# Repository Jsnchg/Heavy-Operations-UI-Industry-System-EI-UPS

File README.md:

# Heavy-Operations-UI-Industry-System-EI-UPS

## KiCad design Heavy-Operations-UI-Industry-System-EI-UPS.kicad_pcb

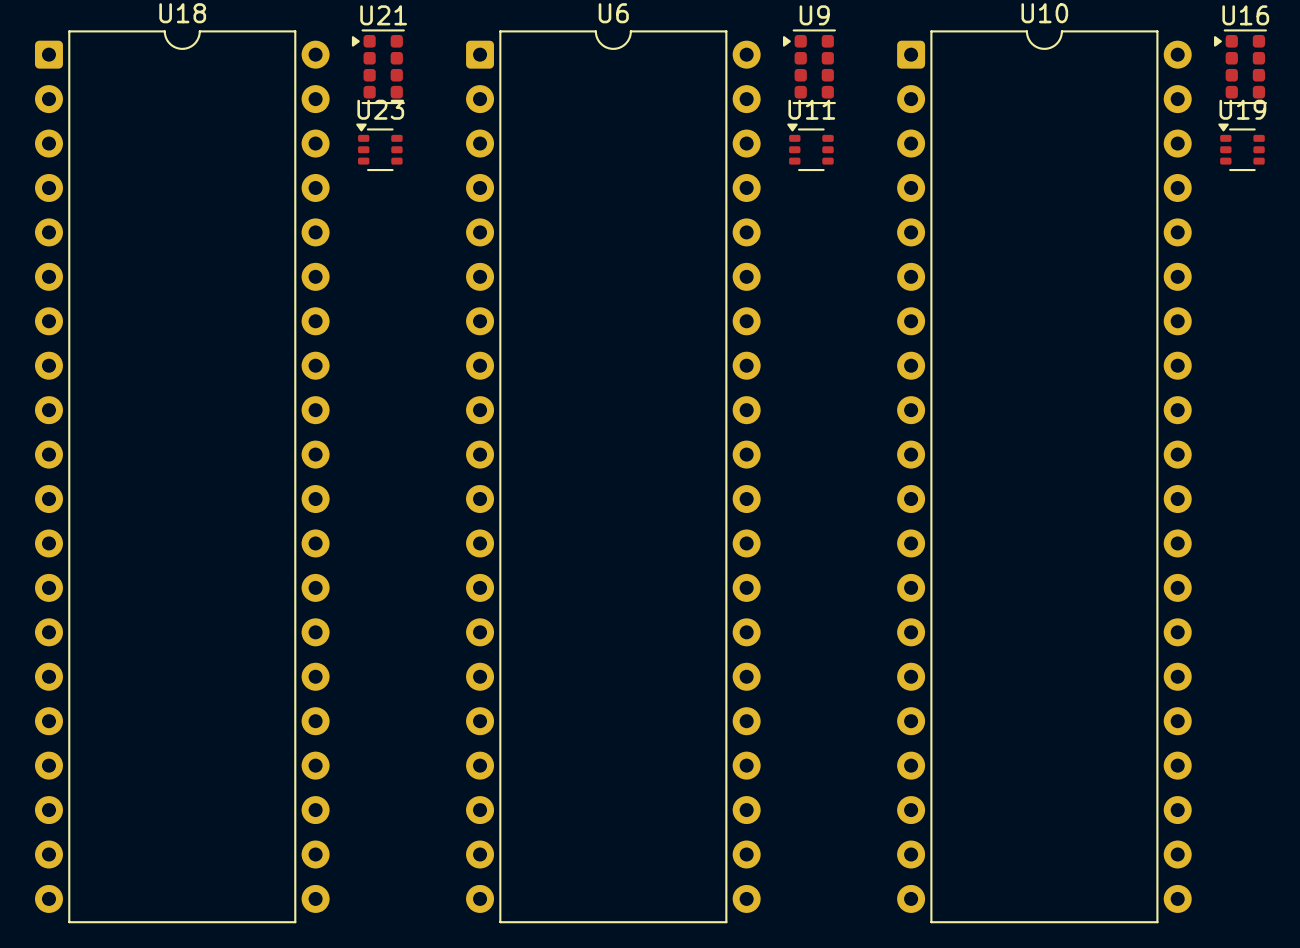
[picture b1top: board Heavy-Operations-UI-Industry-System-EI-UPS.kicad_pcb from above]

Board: 2 copper layers, 9 parts (0 on the bottom side), 6 nets, no tracks yet.

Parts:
U6, U10, U18: 8080; DIP-40_W15.24mm
U9, U16, U21: RPR-0521RS; Rohm_RPR-0521RS
U11, U19, U23: NCS210; SOT-363_SC-70-6

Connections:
unnamed: U10.33 (A7), U19.5 (-IN)
unnamed: U6.33 (A7), U11.5 (-IN)
unnamed: U9.3 (GND), U11.3 (Vs)
unnamed: U16.3 (GND), U19.3 (Vs)
unnamed: U18.33 (A7), U23.5 (-IN)
unnamed: U21.3 (GND), U23.3 (Vs)

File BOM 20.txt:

Heavy-Operations-UI-Industry-System-EI-UPS
BOM 20

A. Uninterruptible Power Supply
1. AC
2. +BATT
3. D_Capacitance

B. Offline UPS
1. AC
2. NCP730
3. NMOS x2
4. NIS3071
5. Battery
6. NCP51752
7. 8080
8. NCV7340
9. SWITCH
10. RPR-0521RS
11. NCS210
12. CAT24C64
13. D_Capacitance

C. Online UPS
1. AC
2. NCP730
3. NMOS x3
4. Q_NIGBT_CEG
5. NIS3071
6. Battery
7. NCP51752
8. 8080
9. NCV7340
10. RPR-0521RS
11. NCS210
12. CAT24C64
13. D_Capacitance

D. Line-Interactive UOS
1. AC
2. NCP730
3. R
4. NMOS x2
5. NIS3071
6. Battery
7. NCP51752
8. 8080
9. NCV7340
10. SWITCH
11. RPR-0521RS
12. NCS210
13. CAT24C64
14. D_Capacitance

Total:
1. AC x3
2. NCP730 x3
3. NMOS x7
4. NIS3071 x3
5. Battery x3
6. NCP51752
7. 8080 x3
8. NCV7340 x3
9. SWITCH x3
10. RPR-0521RS x3
11. NCS210 x3
12. CAT24C64 x3
13. D_Capacitance x3
14. R

Note:
Components 13 and 14 was added to make the project more unique
